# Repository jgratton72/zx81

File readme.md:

# ZX81 Rev C – KiCad 9 Conversion

This repository contains a KiCad 9 conversion of the **Bluescreen2001 ZX81 Rev C** schematic and PCB. Originally designed in Eagle, this version has been fully migrated to KiCad for improved accessibility, maintainability, and future-proofing.

## 🔧 Project Highlights

- ✅ Full schematic and PCB layout migrated to **KiCad 9**
- 📦 Includes an **interactive BOM (iBOM)** for streamlined assembly and part sourcing
- 🧩 Preserves original routing and component placement for legacy compatibility
- 🛠️ Modular file structure for easy editing and future expansion

## 📁 File Overview

- `zx81c/zx81.kicad_sch` – KiCad 9 schematic
- `zx81c/zx81.kicad_pcb` – KiCad 9 PCB layout
- `zx81c/zx81.kicad_pro` – KiCad project file
- `zx81.kicad_prl` – Project local settings
- `zx81c/zx81-eagle-import.kicad_sym` – Symbol library from Eagle import
- `zx81c/sym-lib-table` – Symbol library table
- `zx81c/fp-info-cache` – Footprint cache
- `zx81c/bom/` – iBOM files for interactive part placement and sourcing
- `zx81c/pdf/` – PDF file for the schematic

## 📦 iBOM Integration

This project includes an iBOM (interactive BOM) generated from the KiCad layout. To view it:

1. Open the `bom/` folder.
2. Launch the HTML file in your browser.
3. Use the interactive interface to identify components, placement, and sourcing info.

For more on iBOM, visit the [iBOM GitHub page](https://github.com/openscopeproject/InteractiveHtmlBom).

## 🧠 Notes

- This conversion retains the original ZX81 Rev C design intent while enabling modern workflows.
- All files are compatible with KiCad 9.x and later.
- Contributions and forks welcome—especially for modular enhancements or enclosure integration.

## 🙌 Credits

- Original design by [bluescreen2001](https://github.com/bluescreen2001)
- KiCad 9 conversion and iBOM integration by [jgratton72](https://github.com/jgratton72)

---

Feel free to open issues or submit pull requests for improvements, documentation, or hardware compatibility overlays.

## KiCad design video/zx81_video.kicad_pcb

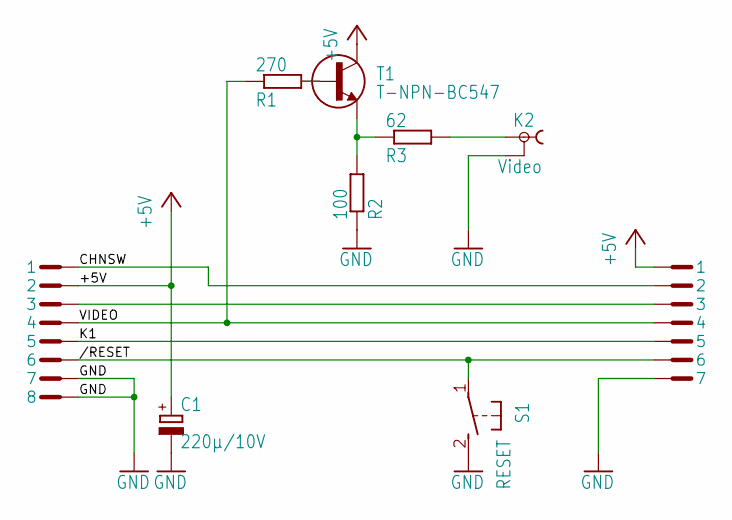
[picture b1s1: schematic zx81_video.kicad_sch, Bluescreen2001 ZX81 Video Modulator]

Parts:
C1: 220µ/10V; E2,5-6
K2: Video; TOBU3
K3: PINHEAD-1X7; PINHEAD1X7
K6: PINHEAD-2X4; PINHEAD2X4
R1: 270; R207_10
R2: 100; R207_10
R3: 62; R207_10
S1: RESET; B3F-31XX
T1: T-NPN-BC547; TO92

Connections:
+5V: C1.+, K3.1, K6.2, T1.C
/RESET: K3.6, K6.6, S1.1
CHNSW: K3.2, K6.1
GND: C1.-, K2.2, K2.2@1 (2), K2.2@2 (2), K3.7, K6.7, K6.8, R2.1, S1.2 (S)
K1: K3.5, K6.5
unnamed: K3.3, K6.3
unnamed: R1.2, T1.B
unnamed: R2.2, R3.1, T1.E
unnamed: K2.1, R3.2
VIDEO: K3.4, K6.4, R1.1

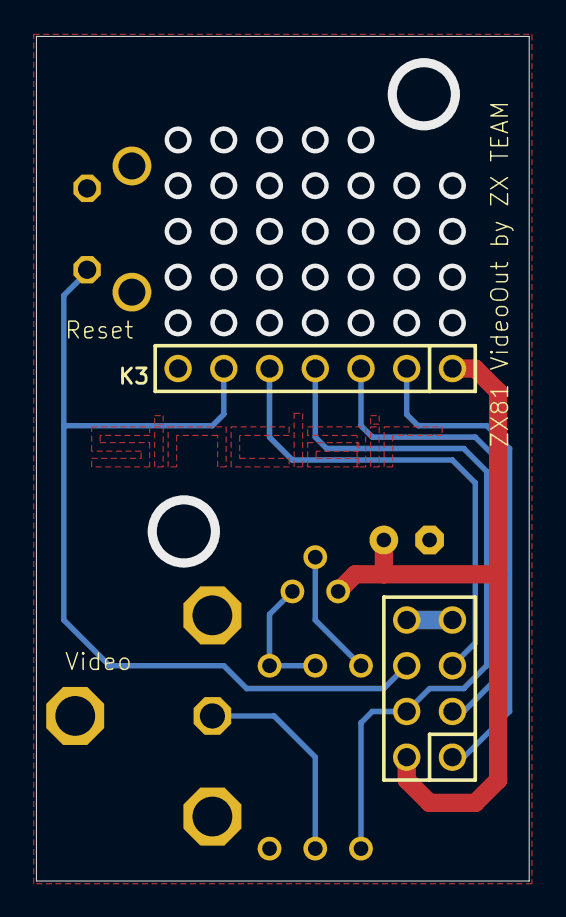
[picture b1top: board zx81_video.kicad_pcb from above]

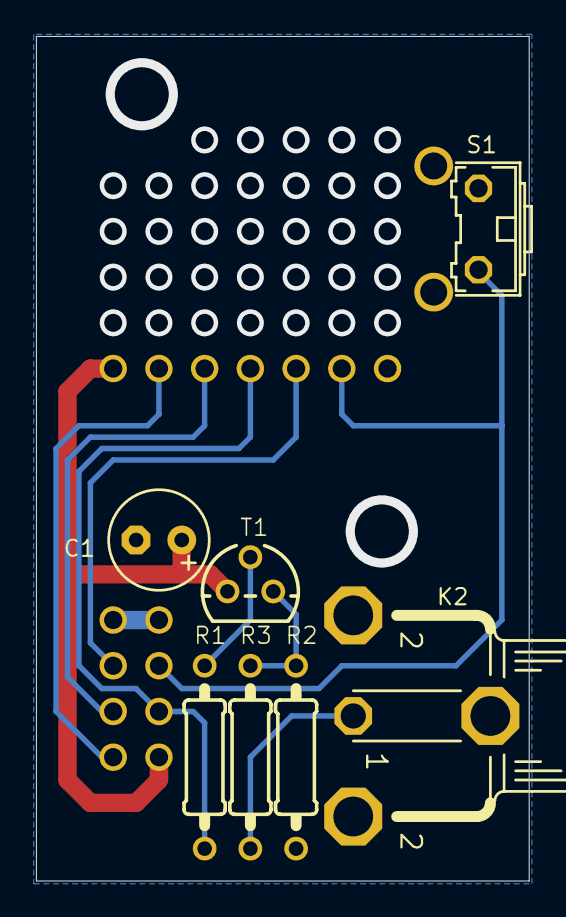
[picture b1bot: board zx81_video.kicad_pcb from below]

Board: 2 copper layers, 27.4 x 46.9 mm, 9 parts (7 on the bottom side), 10 nets.

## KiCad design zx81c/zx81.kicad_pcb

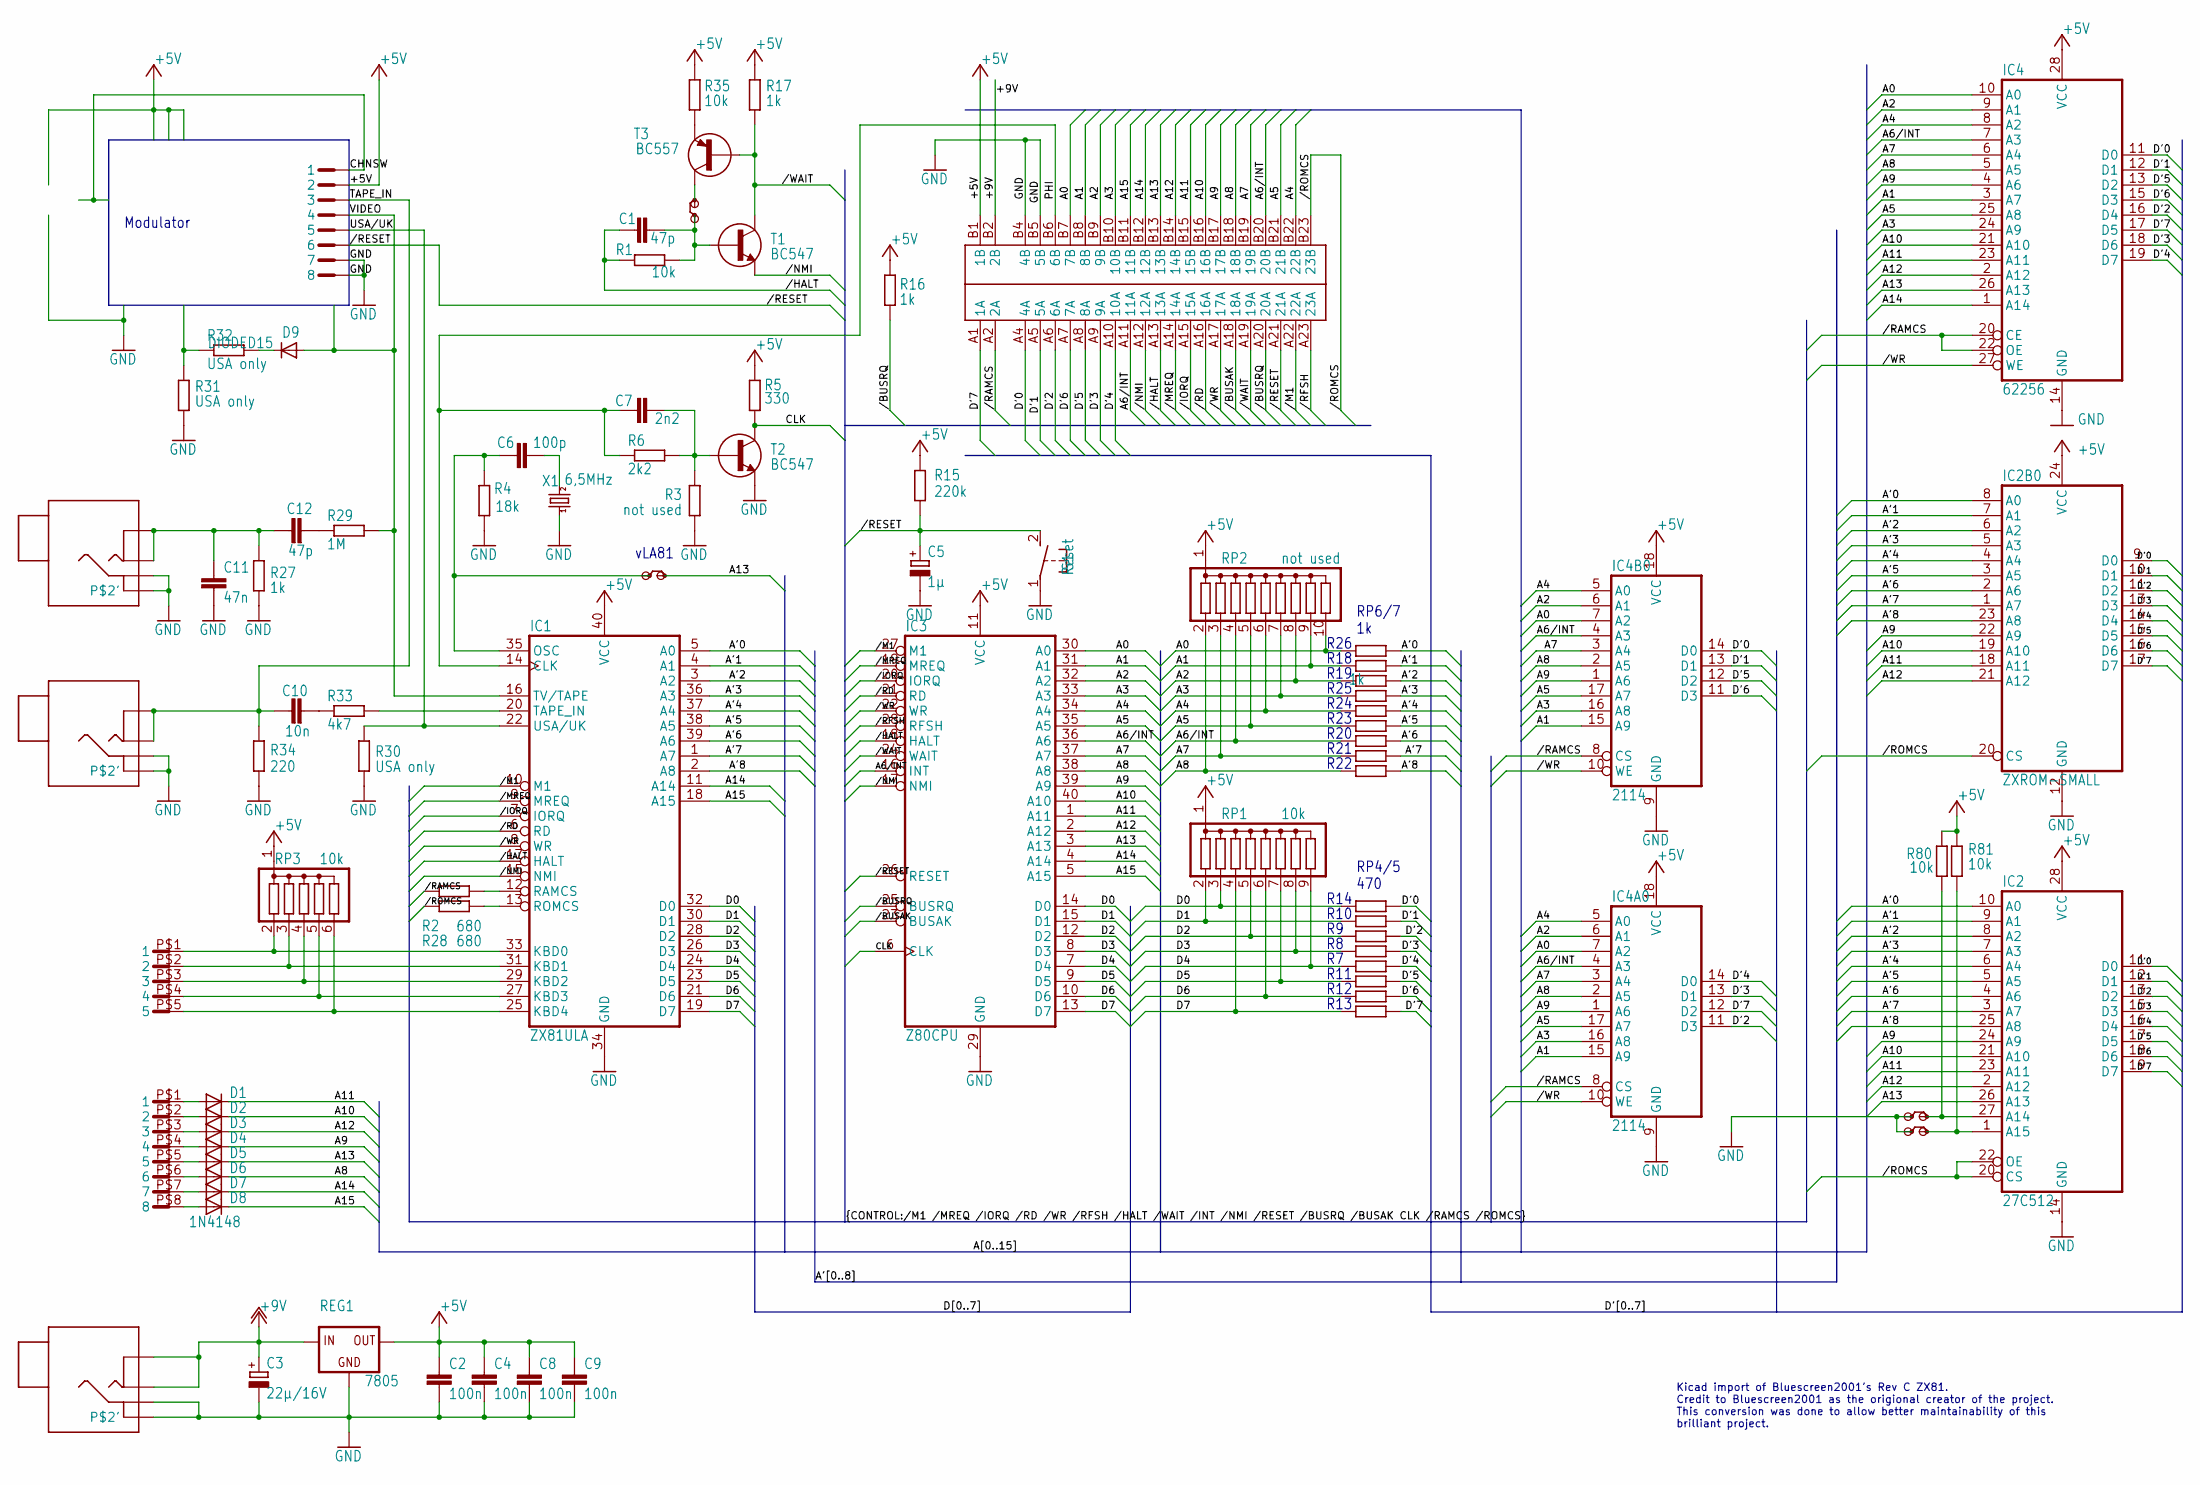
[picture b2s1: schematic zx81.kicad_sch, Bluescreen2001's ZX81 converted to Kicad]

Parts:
C1, C12: 47p; C025-025X050
C2, C4, C8, C9: 100n; C025-025X050
C3: 22µ/16V; E5-5
C5: 1µ; E3,8-5
C6: 100p; C025-025X050
C7: 2n2; C025-025X050
C10: 10n; C025-025X050
C11: 47n; C025-025X050
D1, D2, D3, D4, D5, D6, D7, D8: 1N4148; D-TR-10
D9: DIODED15; D15
IC1: ZX81ULA; DIL40
IC2: 27C512; DIL28
IC2B0: ZXROM-SMALL; DIL24
IC3: Z80CPU; DIL40
IC4: 62256; DIL28
IC4A0, IC4B0: 2114; DIL18
JP1, JP2, JP3, JP4: JUMPER
K1: ZX81CONN; ZX81CON
K2: MIC; ZXKLINKE4POL
K3: EAR; ZXKLINKE4POL
K4: DCIN; ZXKLINKE4POL
K5: PINHEAD-2X4; PINHEAD2X4
KB1: ZXKBD5CON; ZXKDB5
KB2: ZXKBD8CON; ZXKBD8
R1, R35, R80, R81: 10k; R207_12
R2, R28: 680; R207_12
R3: not used; R207_12
R4: 18k; R207_12
R5: 330; R207_12
R6: 2k2; R207_12
R15: 220k; R207_12
R16, R17, R27: 1k; R207_12
R29: 1M; R207_12
R30, R31, R32: USA only; R207_12
R33: 4k7; R207_12
R34: 220; R207_12
REG1: 7805; 78XXL
RP1: 10k; SIL9
RP2: not used; SIL10
RP3: 10k; SIL6
RP4, RP5: 470; SIL8P
RP6: 1k; SIL8P
RP7: 1k; SIL10P
S1: Reset; B3F-31XX
T1, T2: BC547; TO92
T3: BC557; TO92
X1: 6,5MHz; HC49

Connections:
+5V: C2.1, C4.1, C8.1, C9.1, IC1.40 (VCC), IC2.28 (VCC), IC2B0.24 (VCC), IC3.11 (VCC), IC4.28 (VCC), IC4A0.18 (VCC), IC4B0.18 (VCC), K1.B1 (1B), K5.2, R5.2, R15.2, R16.1, R17.2, R35.2, R80.2, R81.2, REG1.OUT, RP1.1, RP2.1, RP3.1
+9V: C3.+, K1.B2 (2B), K4.1, K4.1', REG1.IN
/BUSAK: IC3.23 (BUSAK), K1.A18 (18A)
/BUSRQ: IC3.25 (BUSRQ), K1.A20 (20A), R16.2
/HALT: C1.1, IC1.17 (HALT), IC3.18 (HALT), K1.A13 (13A), R1.1
/IORQ: IC1.7 (IORQ), IC3.20 (IORQ), K1.A15 (15A)
/M1: IC1.10 (M1), IC3.27 (M1), K1.A22 (22A)
/MREQ: IC1.9 (MREQ), IC3.19 (MREQ), K1.A14 (14A)
/NMI: IC1.15 (NMI), IC3.17 (NMI), K1.A12 (12A), T1.E
/RAMCS: IC4.20 (CE), IC4.22 (OE), IC4A0.8 (CS), IC4B0.8 (CS), K1.A2 (2A), R2.2
/RD: IC1.6 (RD), IC3.21 (RD), K1.A16 (16A)
/RESET: C5.+, IC3.26 (RESET), K1.A21 (21A), K5.6, R15.1, S1.2 (S)
/RFSH: IC3.28 (RFSH), K1.A23 (23A)
/ROMCS: IC2.20 (CS), IC2.22 (OE), IC2B0.20 (CS), K1.B23 (23B), R28.2
/WAIT: IC3.24 (WAIT), K1.A19 (19A), R17.1, T1.C, T3.B
/WR: IC1.8 (WR), IC3.22 (WR), IC4.27 (WE), IC4A0.10 (WE), IC4B0.10 (WE), K1.A17 (17A)
A0: IC3.30 (A0), IC4.10 (A0), IC4A0.7 (A2), IC4B0.7 (A2), K1.B7 (7B), RP2.10, RP6.8 (2)
A1: IC3.31 (A1), IC4.3 (A7), IC4A0.15 (A9), IC4B0.15 (A9), K1.B8 (8B), RP2.9, RP7.1
A2: IC3.32 (A2), IC4.9 (A1), IC4A0.6 (A1), IC4B0.6 (A1), K1.B9 (9B), RP2.8, RP7.4 (2)
A3: IC3.33 (A3), IC4.24 (A9), IC4A0.16 (A8), IC4B0.16 (A8), K1.B10 (10B), RP2.7, RP6.6 (2)
A4: IC3.34 (A4), IC4.8 (A2), IC4A0.5 (A0), IC4B0.5 (A0), K1.B22 (22B), RP2.6, RP6.4 (2)
A5: IC3.35 (A5), IC4.25 (A8), IC4A0.17 (A7), IC4B0.17 (A7), K1.B21 (21B), RP2.5, RP6.2
A6/INT: IC3.16 (INT), IC3.36 (A6), IC4.7 (A3), IC4A0.4 (A3), IC4B0.4 (A3), K1.A11 (11A), K1.B20 (20B), RP2.4, RP7.6 (2)
A7: IC3.37 (A7), IC4.6 (A4), IC4A0.3 (A4), IC4B0.3 (A4), K1.B19 (19B), RP2.3, RP7.8 (2)
A8: D6.C, IC3.38 (A8), IC4.5 (A5), IC4A0.2 (A5), IC4B0.2 (A5), K1.B18 (18B), RP2.2, RP7.10 (2)
A9: D4.C, IC2.24 (A9), IC2B0.22 (A9), IC3.39 (A9), IC4.4 (A6), IC4A0.1 (A6), IC4B0.1 (A6), K1.B17 (17B)
A10: D2.C, IC2.21 (A10), IC2B0.19 (A10), IC3.40 (A10), IC4.21 (A10), K1.B16 (16B)
A11: D1.C, IC2.23 (A11), IC2B0.18 (A11), IC3.1 (A11), IC4.23 (A11), K1.B15 (15B)
A12: D3.C, IC2.2 (A12), IC2B0.21 (A12), IC3.2 (A12), IC4.2 (A12), K1.B14 (14B)
A13: D5.C, IC2.26 (A13), IC3.3 (A13), IC4.26 (A13), JP3.2, K1.B13 (13B)
A14: D7.C, IC1.11 (A14), IC3.4 (A14), IC4.1 (A14), K1.B12 (12B)
A15: D8.C, IC1.18 (A15), IC3.5 (A15), K1.B11 (11B)
A'0: IC1.5 (A0), IC2.10 (A0), IC2B0.8 (A0), RP6.7 (1)
A'1: IC1.4 (A1), IC2.9 (A1), IC2B0.7 (A1), RP7.2
A'2: IC1.3 (A2), IC2.8 (A2), IC2B0.6 (A2), RP7.3 (1)
A'3: IC1.36 (A3), IC2.7 (A3), IC2B0.5 (A3), RP6.5 (1)
A'4: IC1.37 (A4), IC2.6 (A4), IC2B0.4 (A4), RP6.3 (1)
A'5: IC1.38 (A5), IC2.5 (A5), IC2B0.3 (A5), RP6.1
A'6: IC1.39 (A6), IC2.4 (A6), IC2B0.2 (A6), RP7.5 (1)
A'7: IC1.1 (A7), IC2.3 (A7), IC2B0.1 (A7), RP7.7 (1)
A'8: IC1.2 (A8), IC2.25 (A8), IC2B0.23 (A8), RP7.9 (1)
CHNSW: K5.1
CLK: IC3.6 (CLK), R5.1, T2.C
D0: IC1.32 (D0), IC3.14 (D0), RP1.3, RP5.7 (1)
D1: IC1.30 (D1), IC3.15 (D1), RP1.2, RP4.7 (1)
D2: IC1.28 (D2), IC3.12 (D2), RP1.5, RP4.5 (1)
D3: IC1.26 (D3), IC3.8 (D3), RP1.8, RP4.3 (1)
D4: IC1.24 (D4), IC3.7 (D4), RP1.9, RP4.2
D5: IC1.23 (D5), IC3.9 (D5), RP1.7, RP5.2
D6: IC1.21 (D6), IC3.10 (D6), RP1.6, RP5.3 (1)
D7: IC1.19 (D7), IC3.13 (D7), RP1.4, RP5.6 (2)
D'0: IC2.11 (D0), IC2B0.9 (D0), IC4.11 (D0), IC4B0.14 (D0), K1.A4 (4A), RP5.8 (2)
D'1: IC2.12 (D1), IC2B0.10 (D1), IC4.12 (D1), IC4B0.13 (D1), K1.A5 (5A), RP4.8 (2)
D'2: IC2.13 (D2), IC2B0.11 (D2), IC4.16 (D4), IC4A0.11 (D3), K1.A6 (6A), RP4.6 (2)
D'3: IC2.15 (D3), IC2B0.13 (D3), IC4.18 (D6), IC4A0.13 (D1), K1.A9 (9A), RP4.4 (2)
D'4: IC2.16 (D4), IC2B0.14 (D4), IC4.19 (D7), IC4A0.14 (D0), K1.A10 (10A), RP4.1
D'5: IC2.17 (D5), IC2B0.15 (D5), IC4.13 (D2), IC4B0.12 (D2), K1.A8 (8A), RP5.1
D'6: IC2.18 (D6), IC2B0.16 (D6), IC4.15 (D3), IC4B0.11 (D3), K1.A7 (7A), RP5.4 (2)
D'7: IC2.19 (D7), IC2B0.17 (D7), IC4.17 (D5), IC4A0.12 (D2), K1.A1 (1A), RP5.5 (1)
GND: C2.2, C3.-, C4.2, C5.-, C8.2, C9.2, C11.2, IC1.34 (GND), IC2.14 (GND), IC2B0.12 (GND), IC3.29 (GND), IC4.14 (GND), IC4A0.9 (GND), IC4B0.9 (GND), JP1.1, JP2.1, K1.B4 (4B), K1.B5 (5B), K2.2, K2.2', K3.2, K3.2', K4.2, K4.2', K5.7, K5.8, R3.1, R4.1, R27.1, R30.2, R31.1, R34.1, REG1.GND, S1.1, T2.E, X1.1
KBD0: IC1.33 (KBD0), KB1.P$1 (1), RP3.2
KBD1: IC1.31 (KBD1), KB1.P$2 (2), RP3.3
KBD2: IC1.29 (KBD2), KB1.P$3 (3), RP3.4
KBD3: IC1.27 (KBD3), KB1.P$4 (4), RP3.5
KBD4: IC1.25 (KBD4), KB1.P$5 (5), RP3.6
unnamed: IC1.12 (RAMCS), R2.1
unnamed: IC1.13 (ROMCS), R28.1
unnamed: C1.2, JP4.1, R1.2, T1.B
unnamed: C6.2, X1.2
unnamed: C6.1, IC1.35 (OSC), JP3.1, R4.2
unnamed: C7.2, R3.2, R6.2, T2.B
unnamed: D1.A, KB2.P$1 (1)
unnamed: D2.A, KB2.P$2 (2)
unnamed: D3.A, KB2.P$3 (3)
unnamed: D4.A, KB2.P$4 (4)
unnamed: D5.A, KB2.P$5 (5)
unnamed: D6.A, KB2.P$6 (6)
unnamed: D7.A, KB2.P$7 (7)
unnamed: D8.A, KB2.P$8 (8)
unnamed: R35.1, T3.E
unnamed: C10.2, R33.1
unnamed: IC2.27 (A14), JP1.2, R80.1
unnamed: IC2.1 (A15), JP2.2, R81.1
unnamed: JP4.2, T3.C
unnamed: C12.2, R29.1
unnamed: D9.C, R32.2
unnamed: R31.2, R32.1
PHI: C7.1, IC1.14 (CLK), K1.B6 (6B), R6.1
TAPEIN: IC1.20 (TAPE_IN), R33.2
TAPE_IN: C10.1, K3.1, K3.1', K5.3, R34.2
TAPE_OUT: C11.1, C12.1, K2.1, K2.1', R27.2
USA/UK: IC1.22 (USA/UK), K5.5, R30.1
VIDEO: D9.A, IC1.16 (TV/TAPE), K5.4, R29.2

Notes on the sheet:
R18
R13
R23
R14
RP4/5 470
R22
R21
R12
Modulator
R26
R10
Kicad import of Bluescreen2001's Rev C ZX81. Credit to Bluescreen2001 as the origional creator of the project. This conversion was done to allow better maintainability of this brilliant project.
R20
RP6/7 1k
R11
R25
vLA81
R24
R19

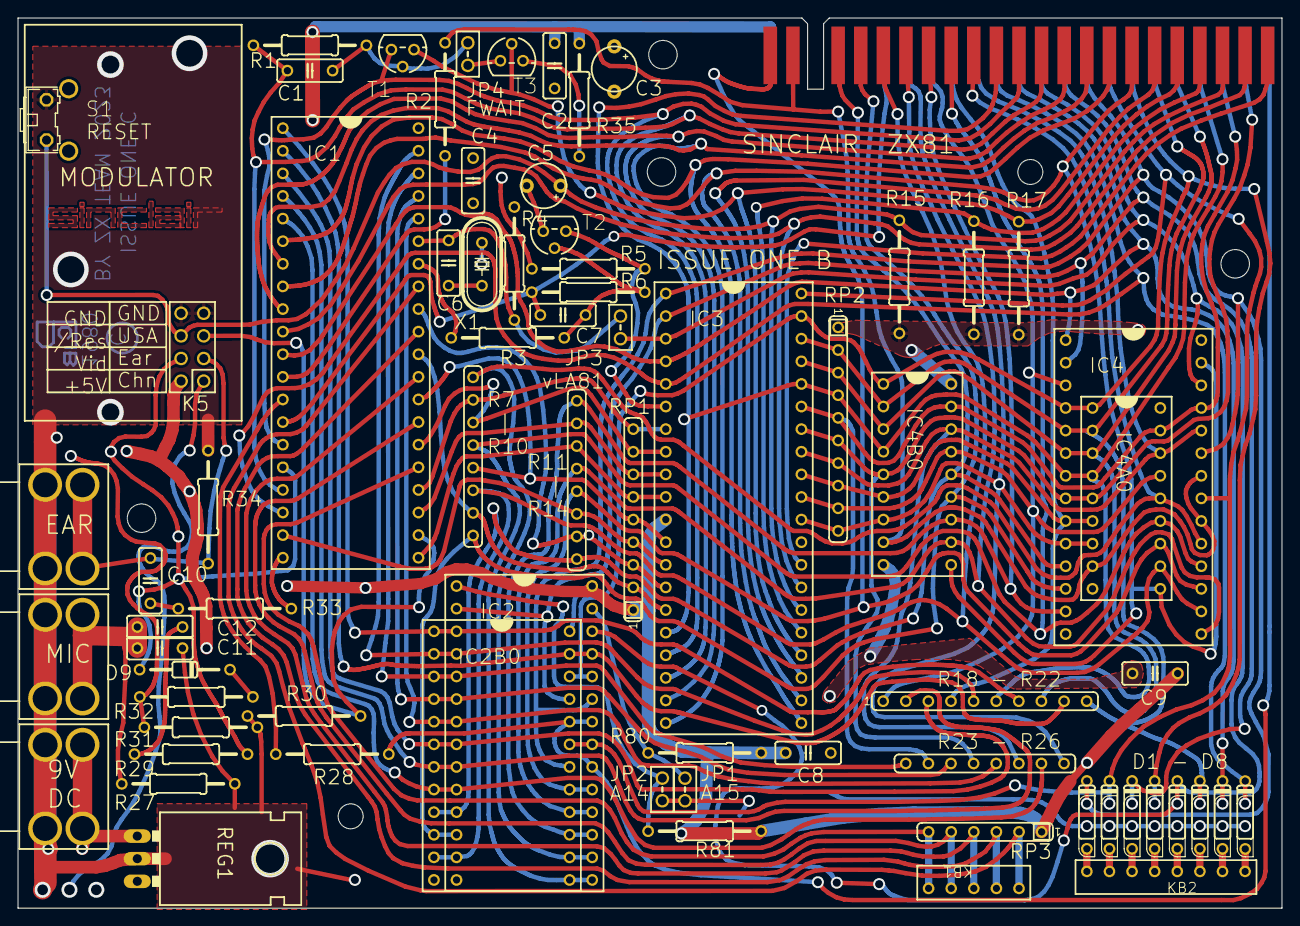
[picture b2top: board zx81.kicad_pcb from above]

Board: 2 copper layers, 142.0 x 100.0 mm, 78 parts (0 on the bottom side), 92 nets.

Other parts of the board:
UNK_HOLE_0: dummyfp0
UNK_HOLE_1: dummyfp1
UNK_HOLE_2: dummyfp2
UNK_HOLE_3: dummyfp3
UNK_HOLE_4: dummyfp4
UNK_HOLE_5: dummyfp5

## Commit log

2025-08-30 new zx81 repo
2025-08-30 added meadme
2025-08-30 updated BOM with via pads
2025-08-30 removed backups
2025-08-30 updated schematic and pcb to include project credits
2025-08-30 created pdf of the schematic
2025-08-30 updated readerme for new folder structure and filenames
2025-08-30 added the video modulator
